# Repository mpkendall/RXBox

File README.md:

# RXBox Zero
### an all-in-one receive station for everything radio

The goal of this project is to sucessfully integrate an SBC (single-board computer), SDR (software-defined radio), touchscreen display, and a lithium battery powerpath into a single cohesive unit. It will be able to support user-built apps using an easy-to-use API for internal functions. The primary use case is for high-altitude ballooning, which demands real-time radio receive capabilities for trackers like [Tiny4FSK](https://github.com/New-England-Weather-Balloon-Society/Tiny4FSK).

Development progress can be followed in the [JOURNAL.md](/JOURNAL.md) file!

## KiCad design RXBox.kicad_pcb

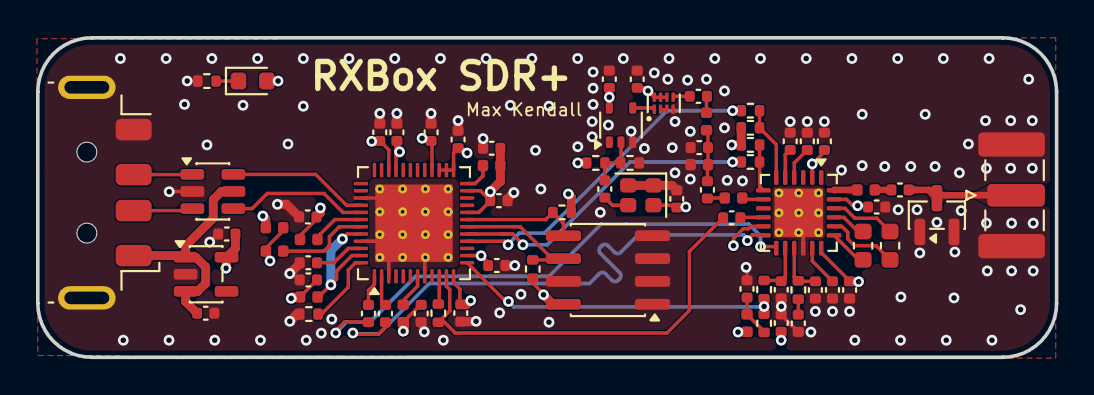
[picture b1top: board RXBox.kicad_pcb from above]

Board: 4 copper layers, 56.6 x 17.8 mm, 75 parts (0 on the bottom side), 54 nets.

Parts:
C1, C5: 20pF; C_0402_1005Metric
C2, C4, C6, C7, C10, C11, C12, C13, C14, C15, C16, C17, C18, C19, C21, C22, C24, C25, C28, C29, C34, C35: 100nF; C_0402_1005Metric
C3: 1.3nF; C_0402_1005Metric
C8, C30, C32, C33: 10uF; C_0402_1005Metric
C9: 47uF; C_0402_1005Metric
C20: 1uF; C_0402_1005Metric
C23, C31: 10nF; C_0402_1005Metric
C26: 330pF; C_0402_1005Metric
C27: 6.8nF; C_0402_1005Metric
C36: 1nF; C_0402_1005Metric
D1: BAV99; SOT-23
D2: LED; LED_0603_1608Metric
J1: SMA; SMA_Samtec_SMA-J-P-H-ST-EM1_EdgeMount
J2: USB_A; USB_A_Molex_48037-2200_Horizontal
L1, L3, L4, L5, L6, L9: bead; L_0402_1005Metric
L2: 4.7uH; L_0402_1005Metric
L7, L8: 150nH; L_0603_1608Metric
L10: 8.2nH; L_0402_1005Metric
L11, L13: 1.6uH; L_0402_1005Metric
L12: 24nH; L_0402_1005Metric
R1, R10: 10kR; R_0402_1005Metric
R2: 1M; R_0402_1005Metric
R3, R4, R5, R6, R11: 4.7kR; R_0402_1005Metric
R7, R8: 220R; R_0402_1005Metric
R9: 1.8kR; R_0402_1005Metric
R12, R13: 100kR; R_0402_1005Metric
R14: 330R; R_0402_1005Metric
U1: RTL2832U; QFN-48-1EP_6x6mm_P0.4mm_EP4.3x4.3mm_ThermalVias
U2: M24C02-WMN; SOIC-8_3.9x4.9mm_P1.27mm
U3: R820T2; QFN-24-1EP_4x4mm_P0.5mm_EP2.7x2.7mm_ThermalVias
U4: AP2112K-3.3; SOT-23-5
U5: 74AUP1G74; X2SON-8_1.4x1mm_P0.35mm
U6: 74LVC1G17; SOT-353_SC-70-5
U7: USBLC6-2SC6; SOT-23-6
X1: 19.2 MHz; Crystal_SMD_2016-4Pin_2.0x1.6mm

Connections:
+1V2: C4.1, C7.1, C9.1, C10.1, C12.1, C15.1, C16.1, C17.1, L2.2, L4.1, L5.1, L6.1, U1.12 (1.2V), U1.20 (1.2V), U1.23 (1.2V), U1.28 (1.2V), U1.34 (1.2V)
+3V3: C18.2, C21.1, C23.2, C25.1, C30.2, C33.1, C34.1, C35.1, D2.2 (A), L3.1, L9.1, R3.1, R4.1, R5.1, R6.1, R12.2, U2.8 (VCC), U3.2 (VCC), U3.11 (VCC), U3.18 (VCC), U3.23 (VCC), U4.5 (VOUT), U5.6 (~CLR), U5.7 (~PRE), U5.8 (VCC), U6.5 (VCC), X1.4 (Vcc)
/sdr/1V2_FILT_1: L4.2, U1.44 (1.2V), U1.47 (1.2V)
/sdr/1V2_FILT_2: L5.2, U1.7 (1.2V)
/sdr/1V2_FILT_3: L6.2, U1.42 (1.2V)
/sdr/BAND_PASS: C1.1, U5.5 (Q)
/sdr/D: U5.2 (D), U5.3 (~Q)
/sdr/EEPROM_SCL: R4.2, U1.18 (EEPROM_SCL), U2.6 (SCL)
/sdr/EEPROM_SDA: R3.2, U1.19 (EEPROM_SDA), U2.5 (SDA)
/sdr/IF_AGC: C28.1, R10.1, U3.14 (IF_AGC)
/sdr/IF_I_N: C14.2, U1.2 (IF_I_N)
/sdr/IF_I_P: C13.2, U1.1 (IF_I_P)
/sdr/IF_N: C14.1, U3.12 (IF_N)
/sdr/IF_P: C13.1, U3.13 (IF_P)
/sdr/RTL_3V3: C6.1, C8.1, C11.1, L1.2, L3.2, U1.14 (3.3V), U1.25 (3.3V), U1.26 (3.3V), U1.27 (3.3V), U1.33 (3.3V)
/sdr/RTL_CLK: C22.1, R2.1, U1.11 (X_I)
/sdr/RTL_DM: U1.41 (USB_DM), U7.4 (I/O2)
/sdr/RTL_DP: U1.40 (USB_DP), U7.6 (I/O1)
/sdr/RTL_IF_AGC: R10.2, R11.1, U1.13 (AGC1)
/sdr/TUNER_SCL: R7.1, U1.16 (TUNER_SCL)
/sdr/TUNER_SDA: R8.1, U1.17 (TUNER_SDA)
/sdr/TUNER_XIN: L13.2, U3.8 (Xtal_I)
Earth: C2.1, C3.1, C4.2, C6.2, C7.2, C8.2, C9.2, C10.2, C11.2, C12.2, C15.2, C16.2, C17.2, C18.1, C19.1, C20.1, C21.2, C23.1, C24.2, C25.2, C26.2, C27.2, C28.2, C29.1, C30.1, C32.2, C33.2, C34.2, C35.2, D1.1 (K), D1.2 (A), J1.2 (Ext), J2.4 (GND), J2.5 (Shield), L12.2, R1.1, R13.1, R14.2, U1.3 (GND), U1.8 (GND), U1.39 (GND), U1.45 (GND), U1.49 (GND), U2.1 (E0), U2.2 (E1), U2.3 (E2), U2.4 (VSS), U2.7 (~WC), U3.16 (GND), U3.25 (GND), U4.2 (GND), U5.4 (GND), U6.3 (GND), U7.2 (GND), X1.1 (GND/NC), X1.2 (GND)
unnamed: C1.2, L11.1
unnamed: C3.2, C5.1, L11.2, L12.1
unnamed: C5.2, L13.1
unnamed: C27.1, R9.2
unnamed: C29.2, L9.2, R11.2
unnamed: C31.2, L10.1
unnamed: C36.2, R12.1, R13.2, U6.2
unnamed: D2.1 (K), R14.1
unnamed: C31.1, D1.3 (K), J1.1 (In)
unnamed: J2.3 (D+), U7.1 (I/O1)
unnamed: J2.2 (D-), U7.3 (I/O2)
unnamed: L1.1, U1.43 (3.3V)
unnamed: L2.1, U1.24 (1.2V_REG_OUT)
unnamed: C2.2, U1.46 (C)
unnamed: R1.2, U1.48 (R)
unnamed: R2.2, U1.10 (X_O)
unnamed: C22.2, U3.10 (CLK_Out)
unnamed: C26.1, R9.1, U3.15 (CP)
unnamed: C20.2, U3.4 (Det1)
unnamed: C19.2, U3.5 (Det2)
unnamed: L10.2, U3.24 (RF_IN)
unnamed: R5.2, R7.2, U3.6 (SCL)
unnamed: R6.2, R8.2, U3.7 (SDA)
unnamed: L8.1, U3.21 (TF1N)
unnamed: L7.1, U3.22 (TF1P)
unnamed: L8.2, U3.19 (TF2N)
unnamed: L7.2, U3.20 (TF2P)
unnamed: C24.1, U3.17 (VDD_PLL)
unnamed: U5.1 (C), U6.4
unnamed: C36.1, X1.3 (Out)
VBUS: C32.1, J2.1 (VBUS), U4.1 (VIN), U4.3 (EN), U7.5 (VBUS)

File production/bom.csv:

Designator,Footprint,Quantity,Value,LCSC Part #
"C1, C5",0402,2,20pF,
"C10, C11, C12, C13, C14, C15, C16, C17, C18, C19, C2, C21, C22, C24, C25, C28, C29, C34, C35, C4, C6, C7",0402,22,100nF,
C20,0402,1,1uF,
"C23, C31",0402,2,10nF,
C26,0402,1,330pF,
C27,0402,1,6.8nF,
C3,0402,1,1.3nF,
"C30, C32, C33, C8",0402,4,10uF,
C36,0402,1,1nF,
C9,0402,1,47uF,
D1,SOT-23,1,BAV99,
D2,0603,1,LED,
J1,SMA_Samtec_SMA-J-P-H-ST-EM1_EdgeMount,1,SMA,
J2,USB_A_Molex_48037-2200_Horizontal,1,USB_A,
"L1, L3, L4, L5, L6, L9",0402,6,bead,
L10,0402,1,8.2nH,
"L11, L13",0402,2,1.6uH,
L12,0402,1,24nH,
L2,0402,1,4.7uH,
"L7, L8",0603,2,150nH,
"R1, R10",0402,2,10kR,
"R11, R3, R4, R5, R6",0402,5,4.7kR,
"R12, R13",0402,2,100kR,
R14,0402,1,330R,
R2,0402,1,1M,
"R7, R8",0402,2,220R,
R9,0402,1,1.8kR,
U1,QFN-48-1EP_6x6mm_P0.4mm_EP4.3x4.3mm_ThermalVias,1,RTL2832U,
U2,SOIC-8_3.9x4.9mm_P1.27mm,1,M24C02-WMN,
U3,QFN-24-1EP_4x4mm_P0.5mm_EP2.7x2.7mm_ThermalVias,1,R820T2,
U4,SOT-23-5,1,AP2112K-3.3,
U5,X2SON-8_1.4x1mm_P0.35mm,1,74AUP1G74,
U6,SOT-353_SC-70-5,1,74LVC1G17,
U7,SOT-23-6,1,USBLC6-2SC6,C7519
X1,Crystal_SMD_2016-4Pin_2.0x1.6mm,1,19.2 MHz,

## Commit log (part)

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2025-11-23 started routing
2025-12-24 done?
2026-01-25 revive project
2026-01-26 done sdr?!
2026-02-15 lowkey forgot git exists
2026-03-22 starting to add stuff
2026-06-26 push current version
2026-06-26 starting over fresh!
2026-06-27 starting journal :P
2026-06-28 first batch of power
2026-06-29 finish up journal
